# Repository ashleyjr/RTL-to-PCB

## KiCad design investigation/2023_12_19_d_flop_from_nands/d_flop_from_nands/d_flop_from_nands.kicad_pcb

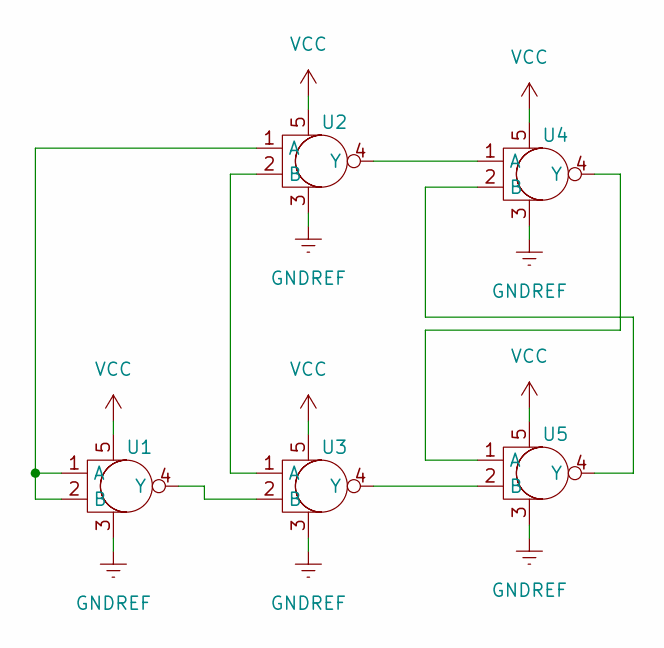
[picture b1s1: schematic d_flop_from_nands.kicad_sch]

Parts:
U1, U2, U3, U4, U5: SN74LVC1G00DCKR

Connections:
GNDREF: U1.3, U2.3, U3.3, U4.3, U5.3
unnamed: U1.1 (A), U1.2 (B), U2.1 (A)
unnamed: U1.4 (Y), U3.2 (B)
unnamed: U2.2 (B), U3.1 (A)
unnamed: U2.4 (Y), U4.1 (A)
unnamed: U3.4 (Y), U5.2 (B)
unnamed: U4.2 (B), U5.4 (Y)
unnamed: U4.4 (Y), U5.1 (A)
VCC: U1.5, U2.5, U3.5, U4.5, U5.5

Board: 2 copper layers, 5 parts (0 on the bottom side), 9 nets, no tracks yet.

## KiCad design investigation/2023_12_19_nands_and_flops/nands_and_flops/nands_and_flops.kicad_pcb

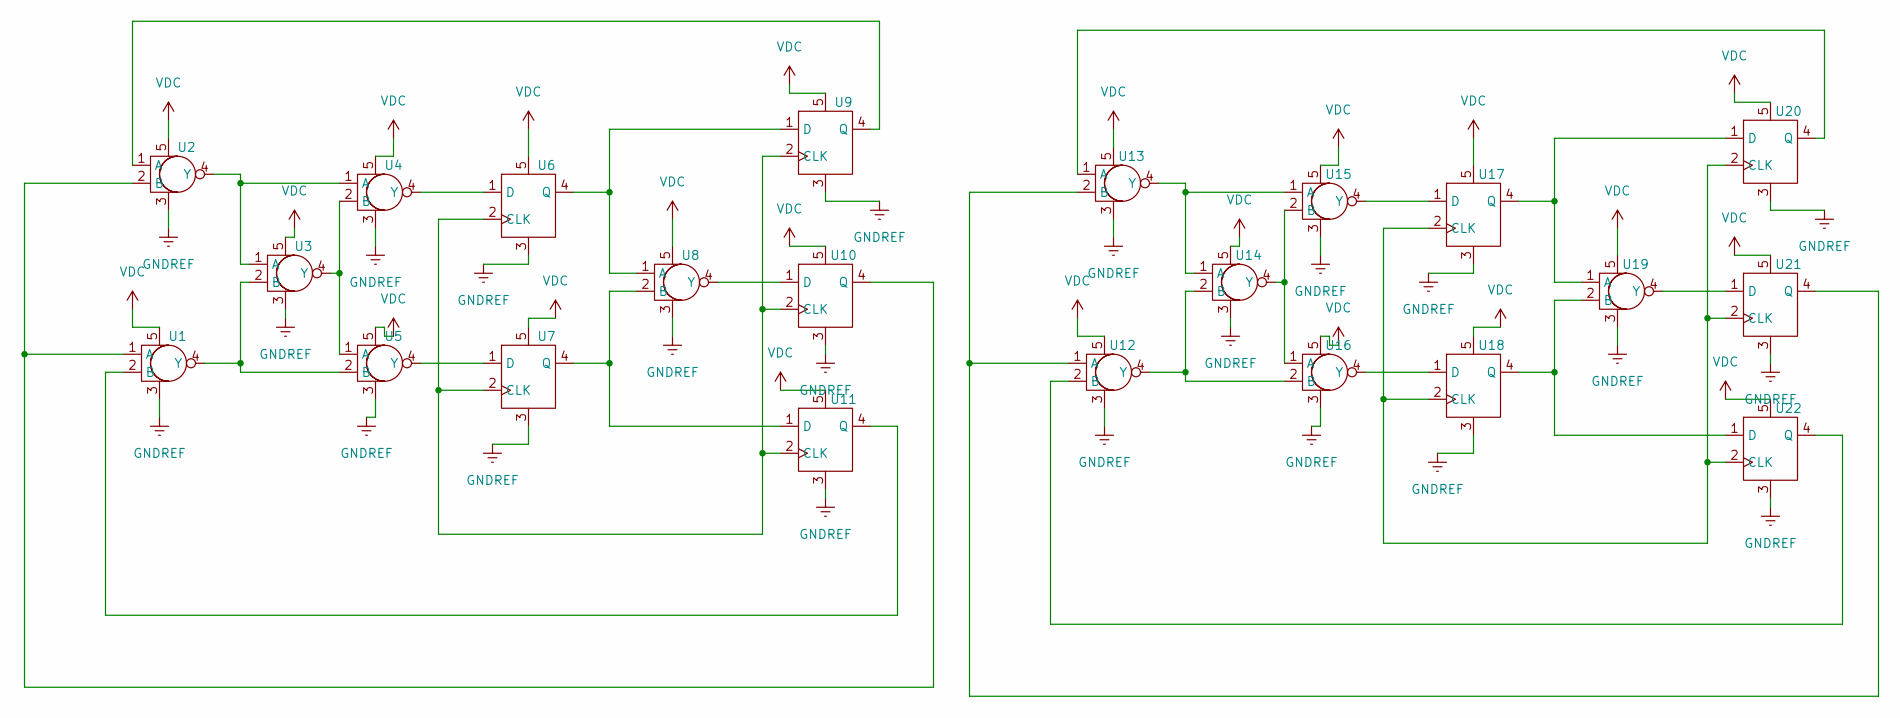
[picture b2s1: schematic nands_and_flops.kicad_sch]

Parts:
U1, U2, U3, U4, U5, U8, U12, U13, U14, U15, U16, U19: SN74LVC1G00DCKR
U6, U7, U9, U10, U11, U17, U18, U20, U21, U22: SN74LVC1G79DCKR; SN74LVC1G00DCKR

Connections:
GNDREF: U1.3, U2.3, U3.3, U4.3, U5.3, U6.3, U7.3, U8.3, U9.3, U10.3, U11.3, U12.3, U13.3, U14.3, U15.3, U16.3, U17.3, U18.3, U19.3, U20.3, U21.3, U22.3
unnamed: U1.1 (A), U2.2 (B), U10.4 (Q)
unnamed: U1.2 (B), U11.4 (Q)
unnamed: U1.4 (Y), U3.2 (B), U5.2 (B)
unnamed: U2.1 (A), U9.4 (Q)
unnamed: U2.4 (Y), U3.1 (A), U4.1 (A)
unnamed: U3.4 (Y), U4.2 (B), U5.1 (A)
unnamed: U4.4 (Y), U6.1 (D)
unnamed: U5.4 (Y), U7.1 (D)
unnamed: U6.4 (Q), U8.1 (A), U9.1 (D)
unnamed: U8.4 (Y), U10.1 (D)
unnamed: U6.2 (CLK), U7.2 (CLK), U9.2 (CLK), U10.2 (CLK), U11.2 (CLK)
unnamed: U7.4 (Q), U8.2 (B), U11.1 (D)
unnamed: U12.1 (A), U13.2 (B), U21.4 (Q)
unnamed: U12.2 (B), U22.4 (Q)
unnamed: U12.4 (Y), U14.2 (B), U16.2 (B)
unnamed: U13.1 (A), U20.4 (Q)
unnamed: U13.4 (Y), U14.1 (A), U15.1 (A)
unnamed: U14.4 (Y), U15.2 (B), U16.1 (A)
unnamed: U15.4 (Y), U17.1 (D)
unnamed: U16.4 (Y), U18.1 (D)
unnamed: U17.2 (CLK), U18.2 (CLK), U20.2 (CLK), U21.2 (CLK), U22.2 (CLK)
unnamed: U17.4 (Q), U19.1 (A), U20.1 (D)
unnamed: U18.4 (Q), U19.2 (B), U22.1 (D)
unnamed: U19.4 (Y), U21.1 (D)
VDC: U1.5, U2.5, U3.5, U4.5, U5.5, U6.5, U7.5, U8.5, U9.5, U10.5, U11.5, U12.5, U13.5, U14.5, U15.5, U16.5, U17.5, U18.5, U19.5, U20.5, U21.5, U22.5

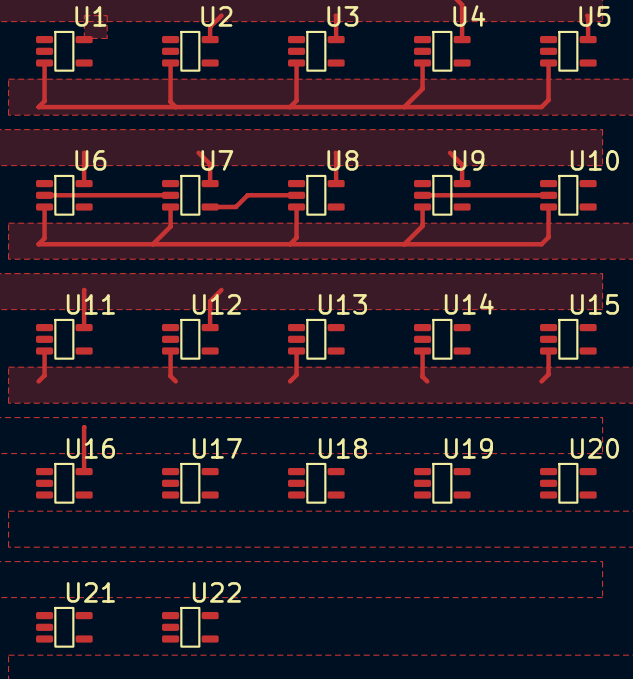
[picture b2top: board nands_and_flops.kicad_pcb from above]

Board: 2 copper layers, 22 parts (0 on the bottom side), 26 nets.

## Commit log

2023-12-27 added first test case
2023-12-28 builds
2023-12-28 shifter
2023-12-28 lib files
2023-12-28 output
2023-12-29 test
2023-12-29 kicad netlist output
2023-12-30 graph
2024-01-01 place
2024-01-01 chnage dict
2024-01-02 add wire crossing
2024-01-05 add router file
2024-01-05 first route
2024-01-11 distance router
2024-01-11 dist route
2024-01-11 rm unused
2024-01-11 first netlist route
2024-01-12 more opt
2024-01-14 another example
2024-01-19 started cpp
2024-01-19 added keepouts
2024-01-20 testing
2024-01-20 schematic
2024-01-21 full
2024-01-22 full test
2024-01-22 first full
2024-01-25 rules
2024-01-26 add ko
2024-01-27 keepout
2024-01-28 dump files
2024-02-01 load pcb
2024-02-01 undo check cells
2024-02-09 debug
2024-02-09 improve layout
2024-02-11 add decap
2024-02-18 mst working
2024-02-19 routing 16 bit counter
2024-02-23 improve mst
2024-02-23 full DRC on 16 bi counter
